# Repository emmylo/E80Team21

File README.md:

# E80

This repository includes Arduino sketches (.ino) for the Teensy on the E80 motherboard.
The files for each lab are included in a separate folder.
The .ino files in each lab folder share the same name as the folder (e.g., `E80_Lab_01.ino` is in a folder named `E80_Lab_01.ino`).
This is a requirement for the Arduino IDE.

This respository also includes a [folder](./libraries/) of all the libraries you need for the various hardware peripherals on your motherboard (e.g., the GPS, and intertial measurement unit (IMU)).

The [MATLAB](./MATLAB/) folder contains the various MATLAB `.m` files which are used throughout the labs.

# How to Use this Repository

## Git Setup
You will need to configure Git on your machine.
Git is a distributed version control system.
This means you can download a local clone of a collection of source code files and easily track the changes that you make to your code.
While we won't be using all the features of git in E80, we will introduce you to the main features that will enable you to interact with the code base for your robot.

First, you need to install Git on your computer.
We recommend that for this class you use [Git Desktop](https://desktop.github.com) which provides a convenient GUI interface for interacting with the code.

1. Download and install the latest version of Git Desktop [here](https://desktop.github.com).
2. Navigate to the [E80 Github repository](https://github.com/HMC-E80/E80) and click `Code > Open with GitHub Desktop`. You will get a prompt to download the repo and Github Desktop will ask you where to save the files. Choose a location on your hard drive where you want to save the files. You should choose a location on your hard drive (e.g., NOT in a folder which is synchronized in the cloud like a Google Drive File Stream folder) to minimize the chances of having any data corrupted. 
   - NOTE: If for some reason clicking `Open with GitHub Desktop` is not working properly, simply copy the URL for the repository (e.g., `https://github.com/HMC-E80/E80`) and then manually clone the repository in GitHub Desktop using `File > Clone Repository`. Enter the copied URL into the "Respository URL" field.

## Arduino IDE Setup
Follow the instructions below to download and use this code within the Arduino IDE.
1. If you have not yet installed the Arduino IDE, install it from [here](https://www.arduino.cc/en/software). The most version as of this writing is 2.0.3 but higher version numbers should also work fine.
2. Follow the instructions [here](https://www.pjrc.com/arduino-ide-2-0-0-teensy-support/) to configure support for the Teensy board within the Arduino IDE.
3. After downloading the code, open the Arduino IDE and go to __Arduino IDE > Settings__ if you are using a MAC and __file > preferences__ if you are using Windows. Change the Sketchbook location to point to the folder you downloaded from Github.

4. Now you if you click on the Sketchbook icon in the toolbar on the left side of the Arduino IDE you should see all the code for your E80 motherboard listed and available. Open up the `E80_Lab_01.ino` sketch and Verify it to check that it compiles and all the libraries are properly downloaded.

Congratulations, you are now set up and have the default E80 source code downloaded!
If you have any issues with these instructions, please reach out to one of the instructors.

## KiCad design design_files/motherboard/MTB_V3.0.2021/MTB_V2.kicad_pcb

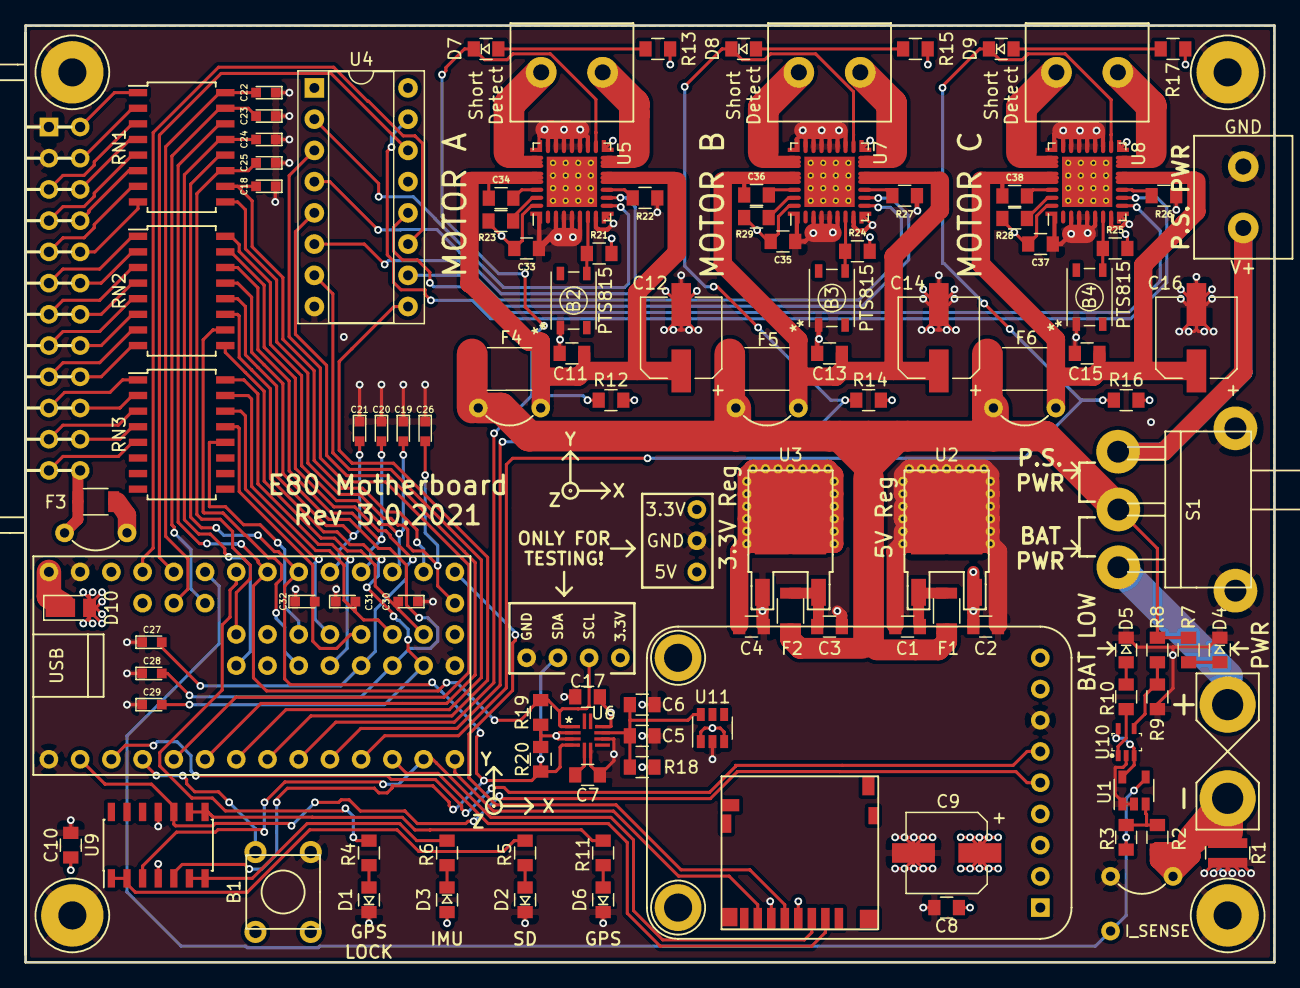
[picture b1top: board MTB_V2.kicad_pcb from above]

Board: 4 copper layers, 101.6 x 76.2 mm, 128 parts (0 on the bottom side), 115 nets.

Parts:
B1: Button; Push_Button
B2, B3, B4: PTS815; PTS815_SJK_250_SMTR_LFS
BT1: Battery; Battery_Connector
C1: 0.33uF; 0805
C2, C6, C7, C8, C10, C11, C13, C15, C17, C33, C34, C35, C36, C37, C38: 0.1uF; 0805
C3, C4, C5: 10uF; 0805
C9, C12, C14, C16: 100uF; CP_Elec_6.3x7.7
C18, C19, C20, C21, C22, C23, C24, C25, C26, C27, C28, C29, C30, C31, C32: 0.1uF; 0603
D1, D2, D3, D4, D5, D6, D7, D8, D9: LED; 0805_Diode
D10: D_Schottky; D_PowerDI-123
F1, F2, F3: 0.5A; 1206
F4, F5, F6: 1.5A; 1812
GPS1: GPS
H1, H2, H3, H4: MOUNTING_HOLE; Mounting_Hole
J1: PTB_CONN
J2: Motor A; 1x2_Screw_Terminal
J3: Motor B; 1x2_Screw_Terminal
J4: Motor C; 1x2_Screw_Terminal
J5: Scew_Terminal_1x2; 1x2_Screw_Terminal
JP1, JP2, JP3, JP4, JP5: Jumper
R1: 0.01; 0612
R2, R12, R14, R16, R19, R20, R21, R23, R24, R25, R28, R29: 10k; 0805
R3: 330k; 0805
R4, R5, R6, R10, R11, R13, R15, R17: 470; 0805
R7: 1.2k; 0805
R8: 30k; 0805
R9: 24k; 0805
R18: 68; 0805
R22, R26, R27: 200; 0805
RN1, RN2, RN3: R_Array_8; SOIC-16W_5.3x10.2mm_Pitch1.27mm
S1: Switch_SPDT; Battery_Switch
SD1: micro_SD; microSD
TP1, TP2, TP3, TP4, TP5, TP6, TP7, TP8: TEST_POINT; Test_Point
TSY1: Teensy3.2; Teensy
U1: MCP6V31; SOT-23-5
U2: L7805; TO-252-3_TabPin2
U3: LD1086; TO-252-3_TabPin2
U4: CD74HC4050; DIP-16_W7.62mm_Socket
U5, U7, U8: MC33HB2002ES; QFN-28_EP_6x6_Pitch0.65mm
U6: SON_03AGRTR_STM; LSM303AGRTR
U9: MCP6004; SOIC-14_3.9x8.7mm_Pitch1.27mm
U10: MCP6541; SC70
U11: LM3880; SOT-23-6

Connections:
1A: TSY1.5, U4.3
1Y: U4.2, U5.8
2A: TSY1.6, U4.5
2Y: U4.4, U5.9
3.3V: C4.1, C8.1, C9.1, C17.1, GPS1.1, R18.1, R19.2, R20.2, SD1.4, TP2.1, TP5.1, U3.2, U6.2, U6.3, U6.10, U11.1, U11.3
3A: TSY1.7, U4.7
3Y: U4.6, U7.8
4A: TSY1.8, U4.9
4Y: U4.10, U7.9
5A: TSY1.25, U4.11
5V: C2.1, C10.1, C33.2, C35.2, C37.2, D3.2, D10.2, R12.2, R13.2, R14.2, R15.2, R16.2, R17.2, R21.2, R23.1, R24.2, R25.2, R28.1, R29.1, TP3.1, U1.5, U2.3, U4.1, U5.28, U7.28, U8.28, U9.4, U10.3, U10.5
5Y: U4.12, U8.8
6A: TSY1.24, U4.14
6Y: U4.15, U8.9
A0: C18.2, RN1.10, TSY1.16
A1: C19.2, RN2.16, TSY1.17
A2: C20.2, RN2.14, TSY1.18
A3: C21.2, RN2.12, TSY1.19
A10: C22.2, RN1.16, TSY1.49
A11: C23.2, RN1.15, TSY1.48
A12: C24.2, RN1.13, TSY1.34
A13: C25.2, RN1.11, TSY1.47
A14: C26.2, RN1.9, TSY1.33
A15: C27.2, RN2.15, TSY1.38
A16: C28.2, RN2.13, TSY1.39
A17: C29.2, RN2.11, TSY1.40
A18: C30.2, RN2.9, TSY1.41
A19: C31.2, RN3.15, TSY1.42
A20: C32.2, RN3.13, TSY1.43
CS: SD1.2, TSY1.12
D24: RN2.10, TSY1.36
D25: RN3.16, TSY1.37
D32: RN3.14, TSY1.44
D33: RN3.12, TSY1.45
EF_A: D7.1, R12.1, TSY1.9, U5.15
EF_B: D8.1, R14.1, TSY1.10, U7.15
EF_C: D9.1, R16.1, TSY1.11, U8.15
GND: B1.1, B2.1, B3.1, B4.1, C1.2, C2.2, C3.2, C4.2, C5.2, C6.2, C7.2, C8.2, C9.2, C10.2, C11.2, C12.2, C13.2, C14.2, C15.2, C16.2, C17.2, C18.1, C19.1, C20.1, C21.1, C22.1, C23.1, C24.1, C25.1, C26.1, C27.1, C28.1, C29.1, C30.1, C31.1, C32.1, C33.1, C35.1, C37.1, D1.1, D2.1, D4.1, D5.1, D6.1, GPS1.7, H1.1, H2.1, H3.1, H4.1, J1.1, J1.2, J5.2, JP2.1, R1.1, R9.1, R22.1, R26.1, R27.1, S1.4, SD1.6, TP4.1, TP8.1, TSY1.1, TSY1.27, TSY1.31, U1.1, U1.2, U2.2, U3.1, U4.8, U5.2, U5.3, U5.4, U5.5, U5.7, U5.16, U5.17, U5.18, U5.19, U5.20, U5.21, U5.29, U5.30, U5.31, U5.32, U5.33, U6.6, U6.8, U7.2, U7.3, U7.4, U7.5, U7.7, U7.16, U7.17, U7.18, U7.19, U7.20, U7.21, U7.29, U7.30, U7.31, U7.32, U7.33, U8.2, U8.3, U8.4, U8.5, U8.7, U8.16, U8.17, U8.18, U8.19, U8.20, U8.21, U8.29, U8.30, U8.31, U8.32, U8.33, U9.11, U10.2, U11.2
I_SENSE: R3.2, TP1.1, TSY1.23, U1.4
MISO: SD1.7, TSY1.14
MOSI: SD1.3, TSY1.13, U9.3
unnamed: B1.2, TSY1.4
unnamed: B2.3, R21.1, U5.6
unnamed: B3.3, R24.1, U7.6
unnamed: B4.3, R25.1, U8.6
unnamed: BT1.1, S1.3
unnamed: BT1.2, JP2.2, R1.2, R2.1
unnamed: C1.1, F1.2, U2.1
unnamed: C3.1, F2.2, U3.3
unnamed: C7.1, U6.5
unnamed: C11.1, C12.1, C34.1, F4.2, JP1.2, U5.11, U5.12, U5.24, U5.25
unnamed: C13.1, C14.1, C36.1, F5.2, JP3.2, U7.11, U7.12, U7.24, U7.25
unnamed: C15.1, C16.1, C38.1, F6.2, JP4.2, U8.11, U8.12, U8.24, U8.25
unnamed: C34.2, U5.26
unnamed: C36.2, U7.26
unnamed: C38.2, U8.26
unnamed: D1.2, R4.1
unnamed: D2.2, R5.1
unnamed: D3.1, R6.1
unnamed: D4.2, R7.1
unnamed: D5.2, R10.1
unnamed: D6.2, R11.1
unnamed: D7.2, R13.1
unnamed: D8.2, R15.1
unnamed: D9.2, R17.1
unnamed: D10.1, TSY1.28
unnamed: F3.2, J1.13, JP5.1
unnamed: J1.3, RN1.3
unnamed: J1.4, RN1.5
unnamed: J1.5, RN1.7
unnamed: J1.6, RN2.1
unnamed: J1.7, RN2.3
unnamed: J1.8, RN2.5
unnamed: J1.9, RN2.7
unnamed: J1.10, RN3.1
unnamed: J1.11, RN3.3
unnamed: J1.12, RN3.5
unnamed: J1.14, RN3.4
unnamed: J1.15, RN3.2
unnamed: J1.16, RN2.8
unnamed: J1.17, RN2.6
unnamed: J1.18, RN2.4
unnamed: J1.19, RN2.2
unnamed: J1.20, RN1.8
unnamed: J1.21, RN1.6
unnamed: J1.22, RN1.4
unnamed: J1.23, RN1.2
unnamed: J1.24, RN1.1
unnamed: J2.1, U5.22, U5.23
unnamed: J2.2, U5.13, U5.14
unnamed: J3.1, U7.22, U7.23
unnamed: J3.2, U7.13, U7.14
unnamed: J4.1, U8.22, U8.23
unnamed: J4.2, U8.13, U8.14
unnamed: J5.1, S1.1
unnamed: R2.2, R3.1, U1.3
unnamed: R4.2, TSY1.22
unnamed: R5.2, U9.1, U9.2
unnamed: R6.2, U9.6, U9.7
unnamed: R8.1, R9.2, U10.4
unnamed: R10.2, U10.1
unnamed: R11.2, U9.8, U9.9
unnamed: R22.2, U5.10
unnamed: R23.2, U5.27
unnamed: R26.2, U8.10
unnamed: R27.2, U7.10
unnamed: R28.2, U8.27
unnamed: R29.2, U7.27
RX: GPS1.5, TSY1.2, U9.10
SCK: SD1.5, TSY1.15
SCL: R19.1, RN1.14, TP6.1, TSY1.21, U6.1
SDA: R20.1, RN1.12, TP7.1, TSY1.20, U6.4, U9.5
TX: GPS1.6, TSY1.3
Vb: F1.1, F2.1, F3.1, F4.1, F5.1, F6.1, JP1.1, JP3.1, JP4.1, JP5.2, R7.2, R8.2, S1.2
Vdd: C5.1, C6.1, R18.2, U6.9, U11.6

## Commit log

2025-03-22 all the files
2025-03-22 reset
2025-03-22 all files
2025-03-25 Changed to buttonSampler
2025-03-26 Update XYStateEstimator.cpp
    4.3 Updates
2025-03-26 change for 4.5
2025-03-29 after jumpstart lab
2025-03-30 changing folder
2025-03-31 office hours commit 1
2025-04-01 creating cpp and h files for anemometer
2025-04-01 created thermistor cpp and h files
2025-04-01 integrating thermistor into default_robot
2025-04-01 don't need these files
2025-04-01 created WindControl files
2025-04-03 after lab
2025-04-07 potentiometer code
2025-04-10 lots of things
2025-04-10 Bin files added
2025-04-11 logreaderfinal
2025-04-11 wind tunnel data
2025-04-14 moved into E80 jail folder
2025-04-15 waypoint things
2025-04-16 pre phake lake
2025-04-16 lake
2025-04-16 at the lake!
2025-04-17 changes for windNav
2025-04-17 matlab
2025-04-18 Calibration Data
2025-04-20 anemometer data
2025-04-21 fixed it?
2025-04-24 tank room
2025-04-24 updated weather vane code
2025-04-26 pre dp
2025-04-26 dp 1
2025-04-27 all sd card data
2025-04-27 find readme file here
2025-04-27 readme
2025-04-27 logreaderfinal: Thermistor and Weather Vane Plot Edits
    edited thermistor and weather vane plots. added time vector for both to scale back to time from sample number. Also, cut off data-->includes now 200-600 seconds for weather vane and greater than 150 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
2025-04-28 weather vane calibration curve
2025-04-28 retry
    push logreaderfinal
2025-05-02 cole look at windVaneReponseGraph.m
2025-05-02 updated filtering
2025-05-02 new weather vane vs heading plots
    new weather vane vs heading plots for separate event to compare
2025-05-02 plots and updated code
    plots of events comparing heading and weather vane angle
2025-05-06 Update thermistorProcess.m
    Steinheart Heart EQ
2025-05-07 copied file

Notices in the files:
parts and their libraries:
Copyright 2021 Accelerated Designs. All rights reserved.
